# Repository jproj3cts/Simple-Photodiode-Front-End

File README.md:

# Simple-Photodiode-Front-End (Work in progress)
This project aims to provide a simple slow (~15KHz) but very cheap and low noise large area photodiode front end, for the use in building scientific instrumentation.

## BILL OF MATERIALS
  ```
PBSS4360PA5-QX
TC1014-3.3VCT713
OPT101P-J
0805 Resistors
0805 Ceramic Capacitors
0805 Tantalum Capacitor (optional)
  ```
 ## Circuit Design

The general scheme of this device is shown below. As can be seen, it is formed of three sections: a capacitance multiplier, a 3.3V regulator, and the OPT101 itself. The first two stages function to minimise input noise as much as possible, with the capacitance multiplier functioning to almost entirely remove mains ripple. The OPT101 is a monolithic photodiode and single-supply transimpedance amplifier, so conveniently amplifies the photodiode output without requiring an external TIA and biases the device too. The disadvantage of course is that it has a relatively limited bandwidth of ~15KHz, but this should be good enough for applications that require only a slow response time such as a spectrophotometer.

 ## Assembly

The PCB itself can be fabricated using your favorite online service by simply uploading the "photodiode for fabrication.zip" file to their online store. I go with JLCPCB, but others are available. Assebly should also be possible using these services if you provide a BOM too, though some special considerations may need to be made for the OPT101 chip since it is an optical component. Elsewise, you can do what I did and hand solder the components.

It is an option to use a tantalum capacitor for C1 to avoid the microphonics associated with ceramic ones. The device can be mounted to a case with a M4 bolt and is designed such that it has no conductive pads on its back and the area around H1 is grounded. As such, if bolted to a conductive case, the case will be grounded and act as an EMI shield. Using only one screw hole also allows fine angluar adjustment of the placement of the photodiode, should that be required.

R2, R3, C4, and C5 are all optional and can be used to set the gain and bandwidth of the detector yourself, details on this are in the OPT101 datasheet (https://www.ti.com/lit/ds/symlink/opt101.pdf). If you would like to use the chip with its internal gain of 1M$`\Omega`$ (0.45 A/W @ 650 nm)  then simply short R3 or C5 and leave the others empty.

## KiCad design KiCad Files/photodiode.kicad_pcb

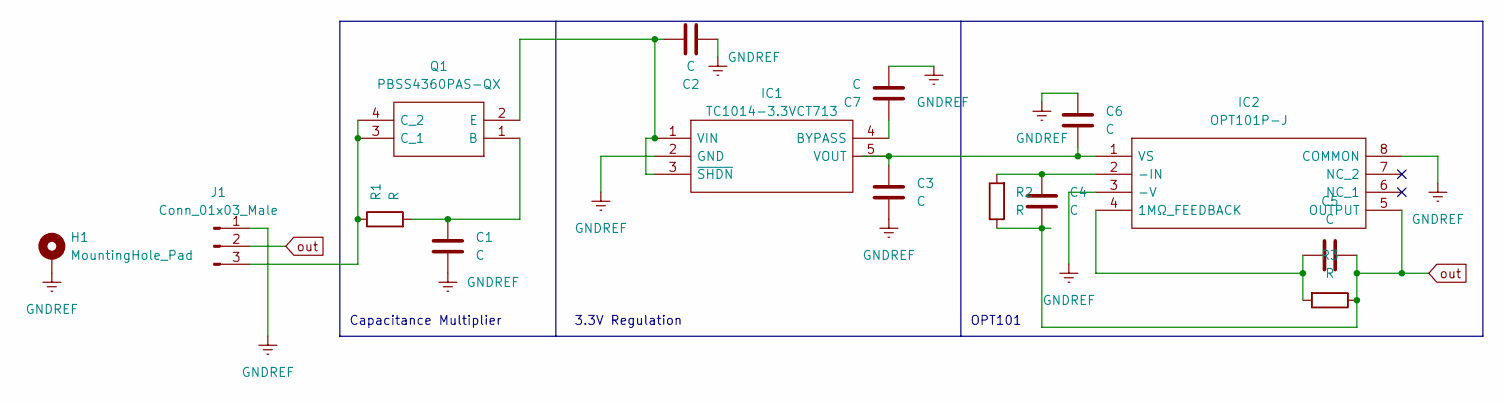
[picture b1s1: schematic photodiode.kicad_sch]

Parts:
C1, C2, C3, C4, C5, C6, C7: C; C_0805_2012Metric_Pad1.18x1.45mm_HandSolder
H1: MountingHole_Pad; MountingHole_4.3mm_M4_Pad
IC1: TC1014-3.3VCT713; SOT95P280X145-5N; Mouser Part Number 579-TC1014-3.3VCT713
IC2: OPT101P-J; OPT101PJ; Mouser Part Number 595-OPT101P-J
J1: Conn_01x03_Male; PinSocket_1x03_P2.54mm_Vertical
Q1: PBSS4360PAS-QX; PBSS4310PASQX; Mouser Part Number 771-PBSS4360PAS-QX
R1, R2, R3: R; R_0805_2012Metric_Pad1.20x1.40mm_HandSolder

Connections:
GNDREF: C1.1, C2.1, C3.1, C6.2, C7.1, H1.1, IC1.2 (GND), IC2.3 (-V), IC2.8 (COMMON), J1.1
unnamed: C1.2, Q1.1 (B), R1.2
unnamed: C2.2, IC1.1 (VIN), IC1.3 (~SHDN), Q1.2 (E)
unnamed: C3.2, C6.1, IC1.5 (VOUT), IC2.1 (VS)
unnamed: C4.2, IC2.2 (-IN), R2.2
unnamed: C5.2, IC2.4 (1MΩ_FEEDBACK), R3.2
unnamed: C7.2, IC1.4 (BYPASS)
unnamed: J1.3, Q1.3 (C_1), Q1.4 (C_2), R1.1
out: C4.1, C5.1, IC2.5 (OUTPUT), J1.2, R2.1, R3.1

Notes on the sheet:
3.3V Regulation
OPT101
Capacitance Multiplier

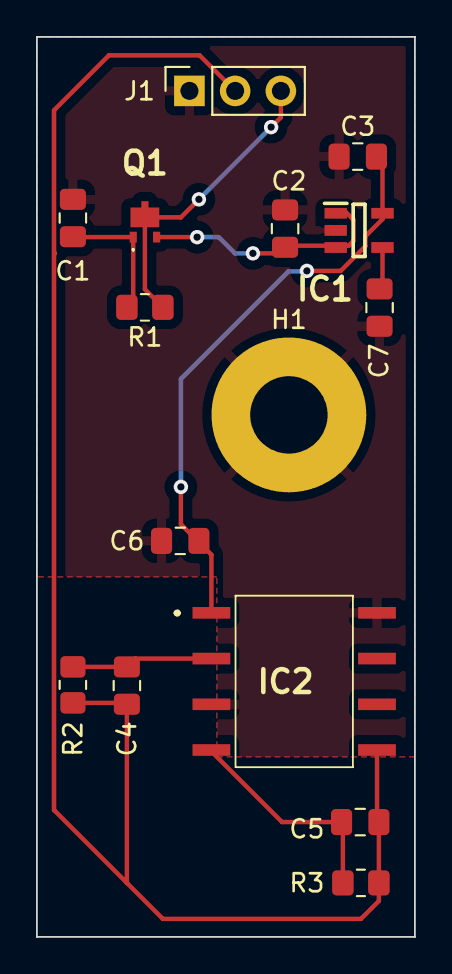
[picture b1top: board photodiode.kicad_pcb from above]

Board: 2 copper layers, 21.0 x 50.0 mm, 15 parts (0 on the bottom side), 9 nets.
